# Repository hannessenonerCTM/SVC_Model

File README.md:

# SVC_Model
A SVC (Static Var Compensation) model for a Educational usecase
To be used with a 110kV overhead line model operated at 1/1000 of the voltage.
Includes 3 TCC (Thyristor Controlled Capacitance) controlled via a 5V SELV control network, optionally a ATMega32U4 can be used for grid voltage regulation. A 5V PSU is included on board. There are no input filters to show the effect of a bad THDi.

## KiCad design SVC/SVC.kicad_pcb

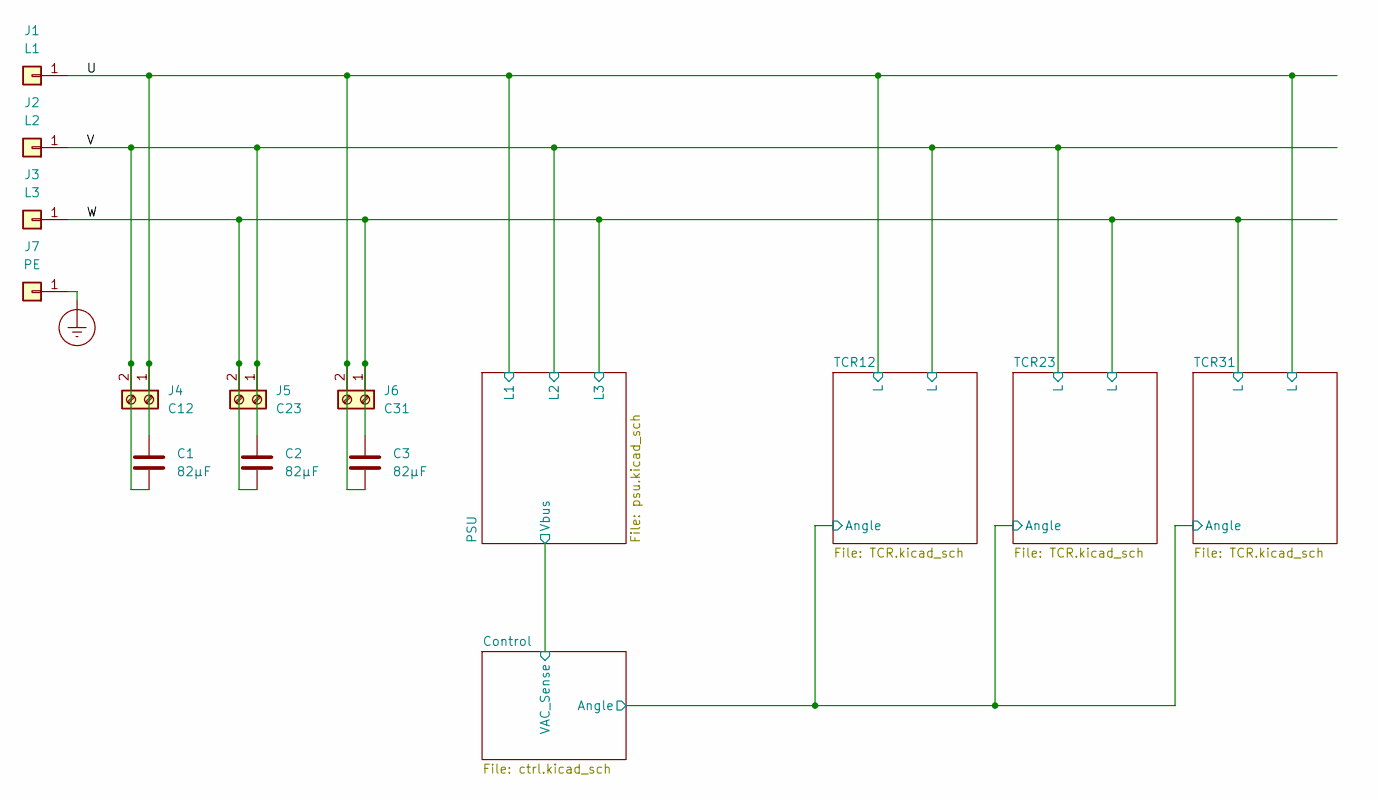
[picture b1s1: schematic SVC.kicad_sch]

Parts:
C1, C2, C3: 82µF
J1: L1; Banana_Jack_1Pin
J2: L2; Banana_Jack_1Pin
J3: L3; Banana_Jack_1Pin
J4: C12; TerminalBlock_bornier-2_P5.08mm
J5: C23; TerminalBlock_bornier-2_P5.08mm
J6: C31; TerminalBlock_bornier-2_P5.08mm
J7: PE; Banana_Jack_1Pin

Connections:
/U: C1.1, C3.2, J1.1, J4.1, J6.2; also elsewhere on the board
/V: C1.2, C2.1, J2.1, J4.2, J5.1; also elsewhere on the board
/W: C2.2, C3.1, J3.1, J5.2, J6.1; also elsewhere on the board
Earth_Protective: J7.1; also elsewhere on the board

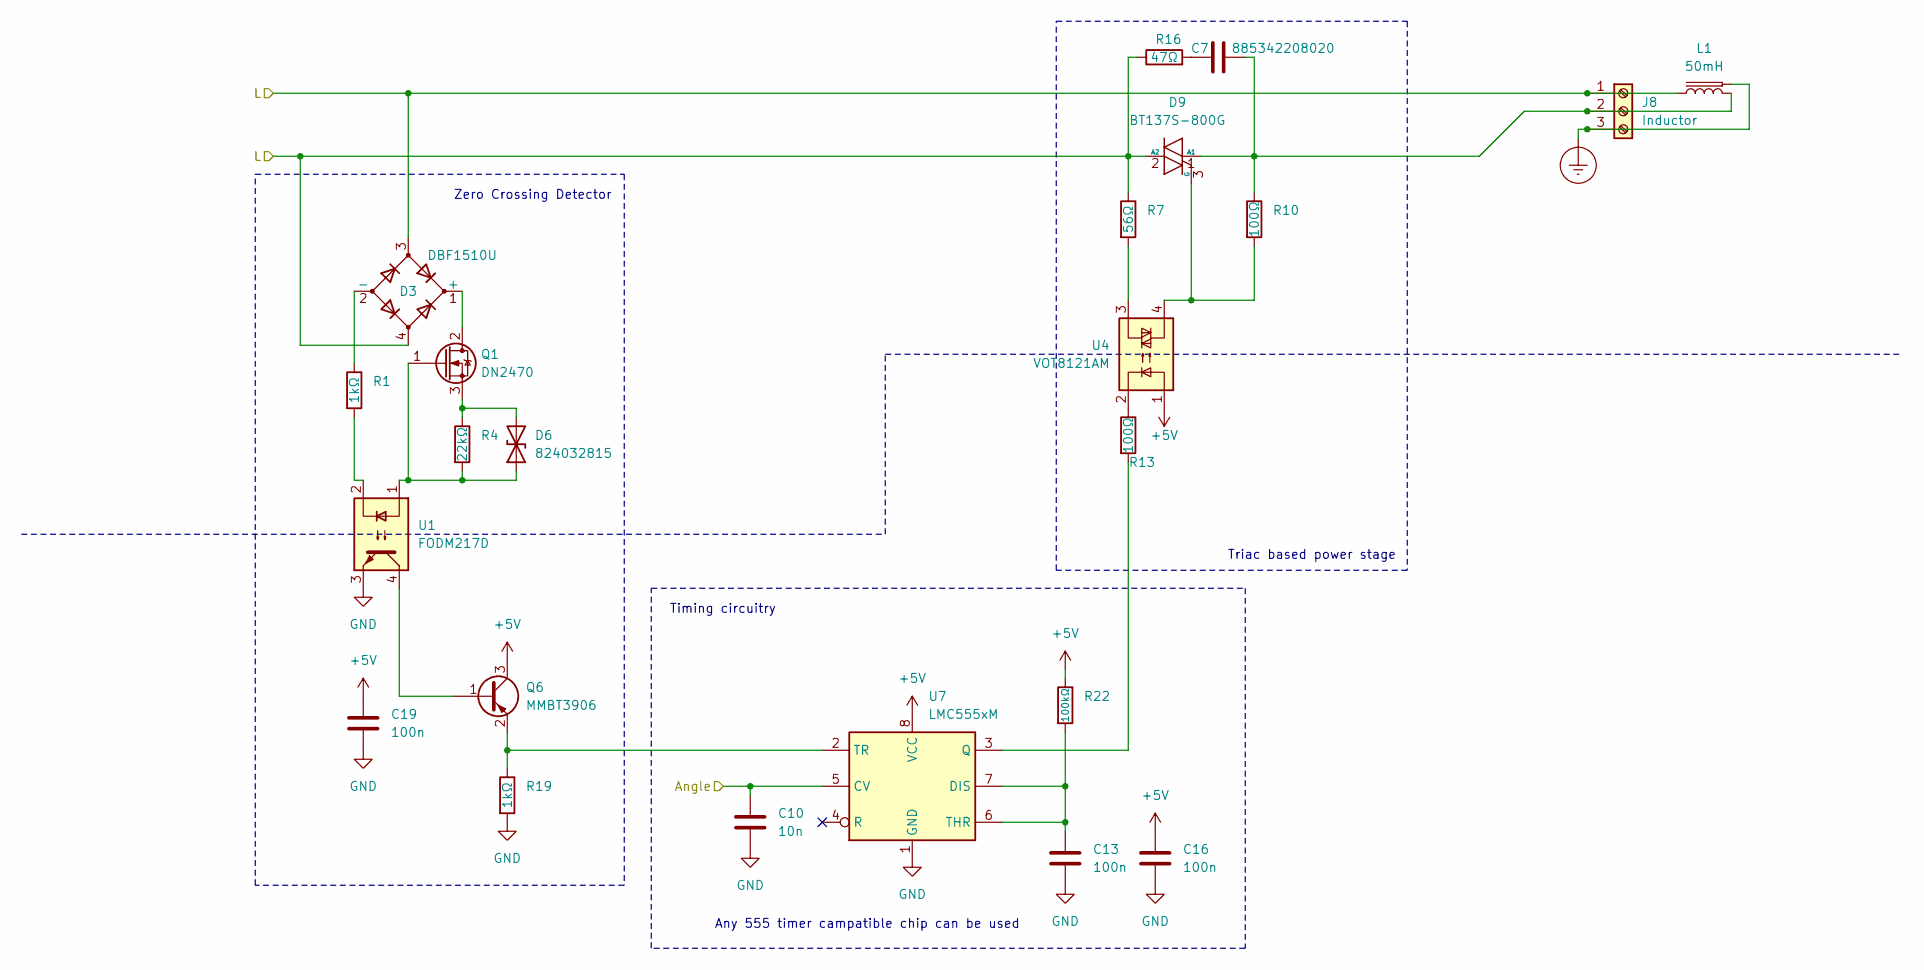
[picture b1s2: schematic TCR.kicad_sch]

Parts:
C7: 885342208020; C_1206_3216Metric
C10: 10n; C_0805_2012Metric
C13, C16, C19: 100n; C_0805_2012Metric
D3: DBF1510U; Diode_Bridge_Diotec_SO-DIL-Slim
D6: 824032815; TVS
D9: BT137S-800G; TO-252-2
J8: Inductor; TerminalBlock_bornier-3_P5.08mm
L1: 50mH
Q1: DN2470; TO-252-2
Q6: MMBT3906; SOT-23
R1, R19: 1kΩ; R_0805_2012Metric
R4: 22kΩ; R_0805_2012Metric
R7: 56Ω; R_1206_3216Metric
R10, R13: 100Ω; R_1206_3216Metric
R16: 47Ω; R_1210_3225Metric
R22: 100kΩ; R_0805_2012Metric
U1: FODM217D; SOP-4_4.4x2.6mm_P1.27mm
U4: VOT8121AM; SOP-4_3.8x4.1mm_P2.54mm
U7: LMC555xM; SOIC-8_3.9x4.9mm_P1.27mm

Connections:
+5V: C16.1, C19.1, Q6.3 (C), R22.1, U4.1, U7.8 (VCC); also elsewhere on the board
/Control/Angle: C10.1, U7.5 (CV); also elsewhere on the board
/U: D3.3, J8.1; also elsewhere on the board
/V: D3.4, D9.2 (A2), R7.1, R16.1; also elsewhere on the board
Earth_Protective: J8.3, L1.2; also elsewhere on the board
GND: C10.2, C13.2, C16.2, C19.2, R19.2, U1.3, U7.1 (GND); also elsewhere on the board
unnamed: C7.1, R16.2
unnamed: D3.1 (+), Q1.2 (D)
unnamed: D3.2 (-), R1.1
unnamed: D6.1 (A1), Q1.1 (G), R4.2, U1.1
unnamed: D6.2 (A2), Q1.3 (S), R4.1
unnamed: C7.2, D9.1 (A1), J8.2, R10.1
unnamed: D9.3 (G), R10.2, U4.4
unnamed: R1.2, U1.2
unnamed: R7.2, U4.3
unnamed: R13.1, U4.2
unnamed: C13.1, R22.2, U7.6 (THR), U7.7 (DIS)
unnamed: R13.2, U7.3 (Q)

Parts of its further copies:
C8, C9: 885342208020; C_1206_3216Metric
C11, C12: 10n; C_0805_2012Metric
C14, C15, C17, C18, C20, C21: 100n; C_0805_2012Metric
D4, D5: DBF1510U; Diode_Bridge_Diotec_SO-DIL-Slim
D7, D8: 824032815; TVS
D10, D11: BT137S-800G; TO-252-2
J9, J10: Inductor; TerminalBlock_bornier-3_P5.08mm
Q2, Q3: DN2470; TO-252-2
Q4, Q5: MMBT3906; SOT-23
R2, R3, R20, R21: 1kΩ; R_0805_2012Metric
R5, R6: 22kΩ; R_0805_2012Metric
R8, R9: 56Ω; R_1206_3216Metric
R11, R12, R14, R15: 100Ω; R_1206_3216Metric
R17, R18: 47Ω; R_1210_3225Metric
R23, R24: 100kΩ; R_0805_2012Metric
U2, U3: FODM217D; SOP-4_4.4x2.6mm_P1.27mm
U5, U6: VOT8121AM; SOP-4_3.8x4.1mm_P2.54mm
U8, U9: LMC555xM; SOIC-8_3.9x4.9mm_P1.27mm

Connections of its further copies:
+5V: C17.1, C18.1, C20.1, C21.1, Q4.3 (C), Q5.3 (C), R23.1, R24.1, U5.1, U6.1, U8.8 (VCC), U9.8 (VCC); also elsewhere on the board
/Control/Angle: C11.1, C12.1, U8.5 (CV), U9.5 (CV); also elsewhere on the board
/U: D5.4, D11.2 (A2), R9.1, R18.1; also elsewhere on the board
/V: D4.3, J9.1; also elsewhere on the board
/W: D4.4, D5.3, D10.2 (A2), J10.1, R8.1, R17.1; also elsewhere on the board
Earth_Protective: J9.3, J10.3; also elsewhere on the board
GND: C11.2, C12.2, C14.2, C15.2, C17.2, C18.2, C20.2, C21.2, R20.2, R21.2, U2.3, U3.3, U8.1 (GND), U9.1 (GND); also elsewhere on the board
unnamed: C8.1, R17.2
unnamed: C9.1, R18.2
unnamed: D4.1 (+), Q2.2 (D)
unnamed: D4.2 (-), R2.1
unnamed: D5.1 (+), Q3.2 (D)
unnamed: D5.2 (-), R3.1
unnamed: D7.1 (A1), Q2.1 (G), R5.2, U2.1
unnamed: D7.2 (A2), Q2.3 (S), R5.1
unnamed: D8.1 (A1), Q3.1 (G), R6.2, U3.1
unnamed: D8.2 (A2), Q3.3 (S), R6.1
unnamed: C8.2, D10.1 (A1), J9.2, R11.1
unnamed: D10.3 (G), R11.2, U5.4
unnamed: C9.2, D11.1 (A1), J10.2, R12.1
unnamed: D11.3 (G), R12.2, U6.4
unnamed: Q5.1 (B), U2.4
unnamed: Q5.2 (E), R20.1, U8.2 (TR)
unnamed: R2.2, U2.2
unnamed: R3.2, U3.2
unnamed: R8.2, U5.3
unnamed: R9.2, U6.3
unnamed: R14.1, U5.2
unnamed: R15.1, U6.2
unnamed: C14.1, R23.2, U8.6 (THR), U8.7 (DIS)
unnamed: R14.2, U8.3 (Q)
unnamed: C15.1, R24.2, U9.6 (THR), U9.7 (DIS)
unnamed: R15.2, U9.3 (Q)

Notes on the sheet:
Timing circuitry
Any 555 timer campatible chip can be used
Zero Crossing Detector
Triac based power stage

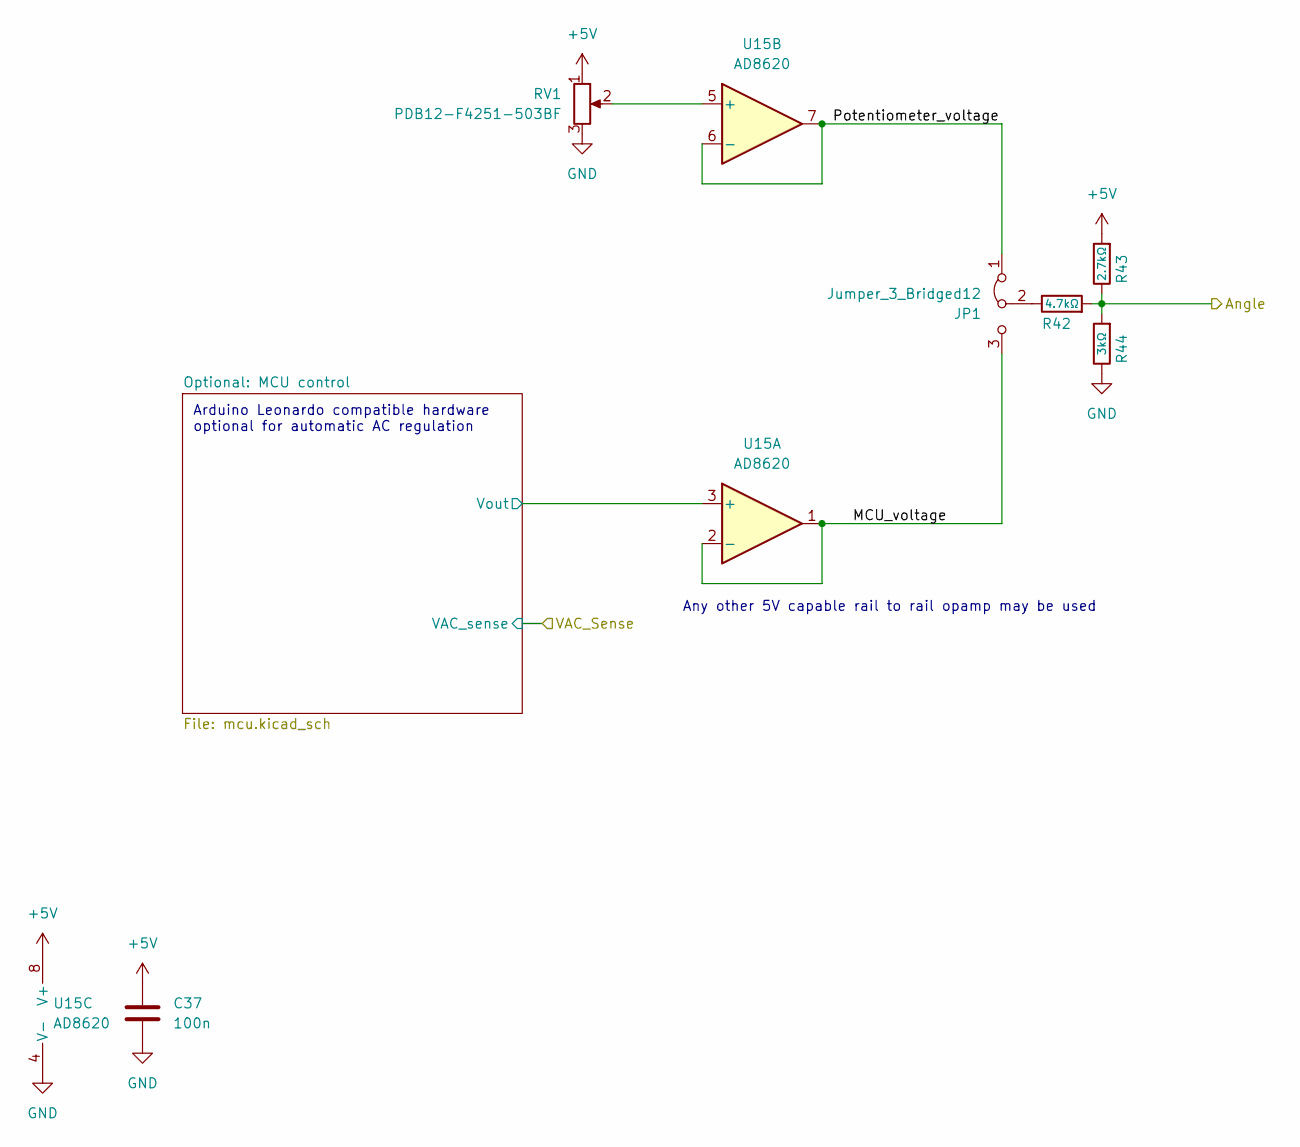
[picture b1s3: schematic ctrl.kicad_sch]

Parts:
C37: 100n; C_0805_2012Metric
JP1: Jumper_3_Bridged12; PinHeader_1x03_P2.54mm_Vertical
R42: 4.7kΩ; R_0805_2012Metric
R43: 2.7kΩ; R_0805_2012Metric
R44: 3kΩ; R_0805_2012Metric
RV1: PDB12-F4251-503BF; Bourns PDB12
U15: AD8620; SOIC-8_3.9x4.9mm_P1.27mm

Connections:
+5V: C37.1, R43.2, RV1.1, U15.8 (V+); also elsewhere on the board
/Control/Angle: R42.2, R43.1, R44.2; also elsewhere on the board
/Control/MCU_voltage: JP1.3 (B), U15.1, U15.2 (-)
/Control/Optional: MCU control/Vout: U15.3 (+); also elsewhere on the board
/Control/Potentiometer_voltage: JP1.1 (A), U15.6 (-), U15.7
GND: C37.2, R44.1, RV1.3, U15.4 (V-); also elsewhere on the board
unnamed: JP1.2 (C), R42.1
unnamed: RV1.2, U15.5 (+)

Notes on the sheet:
Arduino Leonardo compatible hardware optional for automatic AC regulation
Any other 5V capable rail to rail opamp may be used

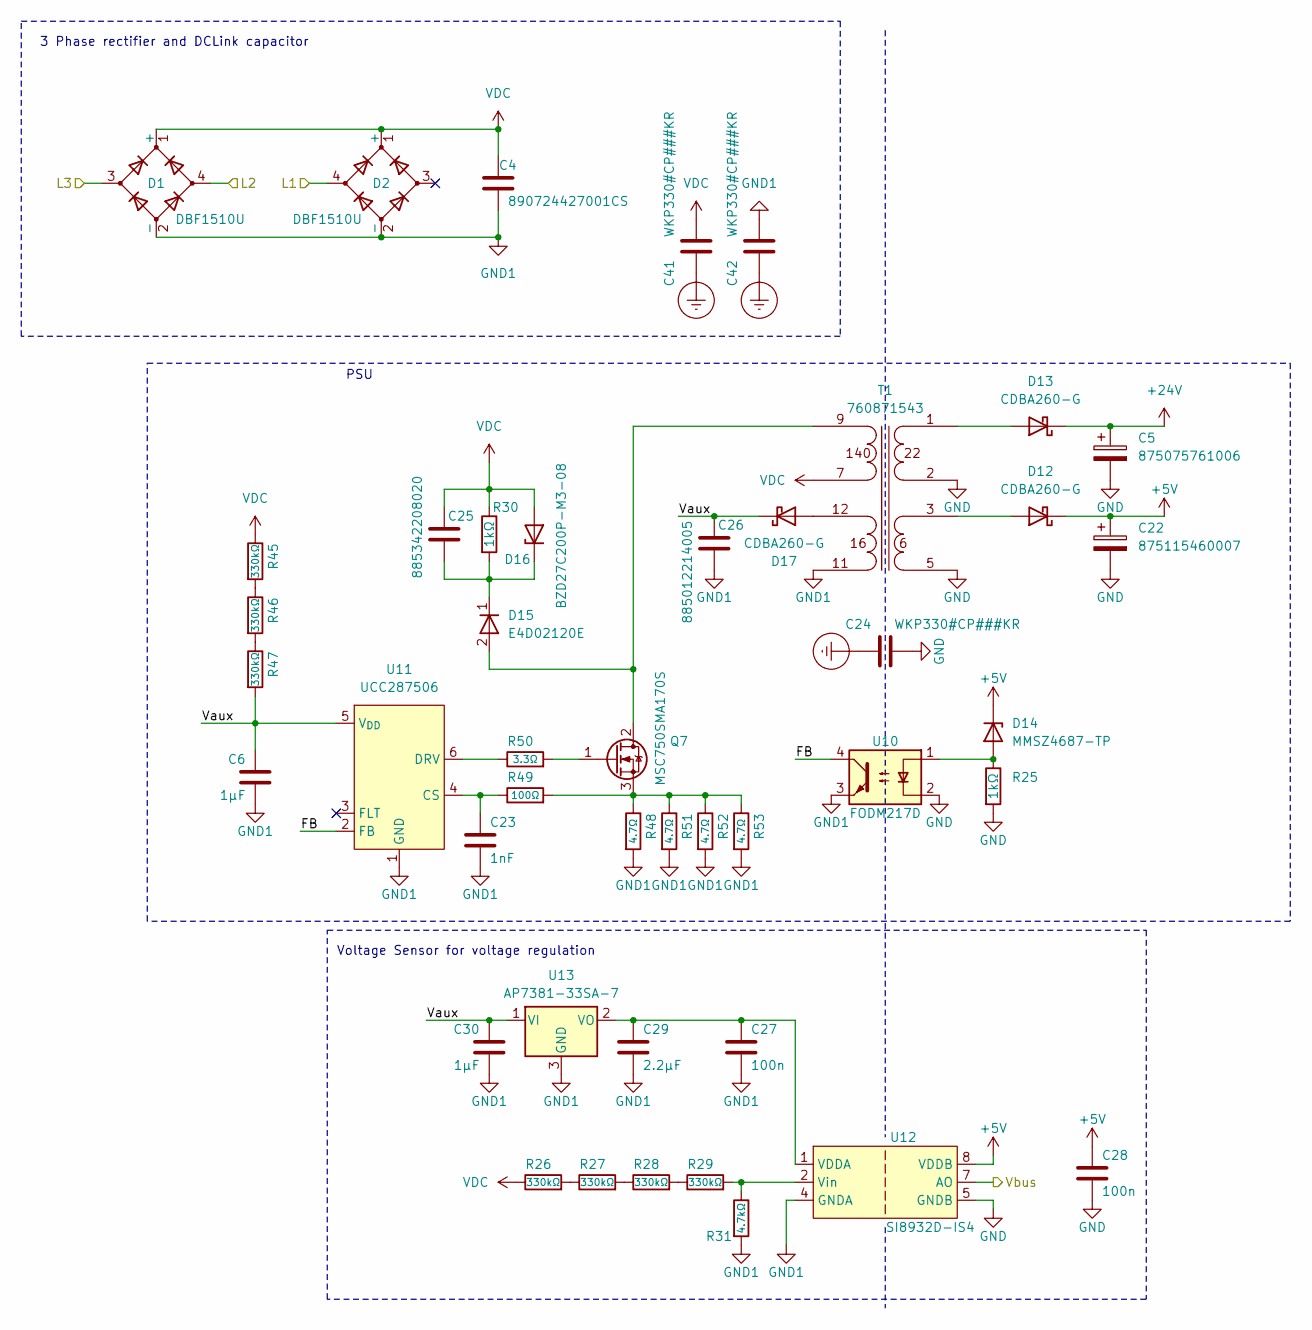
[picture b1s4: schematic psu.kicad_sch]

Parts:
C4: 890724427001CS; C_Rect_L31.5mm_W9.0mm_P27.50mm_MKS4
C5: 875075761006; CP_Elec_10x12.5
C6, C30: 1µF; C_0805_2012Metric
C22: 875115460007; CP_Elec_10x7.9
C23: 1nF; C_0805_2012Metric
C24, C41, C42: WKP330#CP###KR
C25: 885342208020; C_1206_3216Metric
C26: 885012214005; C_1206_3216Metric
C27, C28: 100n; C_0805_2012Metric
C29: 2.2µF; C_0805_2012Metric
D1, D2: DBF1510U; Diode_Bridge_Diotec_SO-DIL-Slim
D12, D13, D17: CDBA260-G; D_SMA
D14: MMSZ4687-TP; D_SOD-123
D15: E4D02120E; TO-252-2_TabPin1
D16: BZD27C200P-M3-08; D_SMF
Q7: MSC750SMA170S; TO-252-2
R25: 1kΩ; R_0805_2012Metric
R26, R27, R28, R29, R45, R46, R47: 330kΩ; R_0805_2012Metric
R30: 1kΩ; R_1206_3216Metric
R31: 4.7kΩ; R_0805_2012Metric
R48, R51, R52, R53: 4.7Ω; R_0805_2012Metric
R49: 100Ω; R_0805_2012Metric
R50: 3.3Ω; R_0805_2012Metric
T1: 760871543
U10: FODM217D; SOP-4_4.4x2.6mm_P1.27mm
U11: UCC287506; SOT-23-6
U12: SI8932D-IS4; SOIC-8_7.5x5.85mm_P1.27mm
U13: AP7381-33SA-7; SOT-23

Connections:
+5V: C22.1, C28.1, D12.1 (K), D14.1 (K), U12.8 (VDDB); also elsewhere on the board
+24V: C5.1, D13.1 (K); also elsewhere on the board
/Control/Optional: MCU control/Arduino Pin A0 ADC: U12.7 (AO); also elsewhere on the board
/PSU/FB: U10.4, U11.2 (FB)
/PSU/Vaux: C6.1, C26.1, C30.1, D17.1 (K), R47.2, U11.5 (V_{DD}), U13.1 (VI)
/U: D2.4; also elsewhere on the board
/V: D1.4; also elsewhere on the board
/W: D1.3; also elsewhere on the board
Earth_Protective: C24.1, C41.1, C42.1; also elsewhere on the board
GND: C5.2, C22.2, C24.2, C28.2, R25.2, T1.2 (OUT1B), T1.5 (OUT2B), T1.6 (OUT2B), U10.2, U12.5 (GNDB), U12.6 (GNDB); also elsewhere on the board
GND1: C4.2, C6.2, C23.2, C26.2, C27.2, C29.2, C30.2, C42.2, D1.2 (-), D2.2 (-), R31.2, R48.2, R51.2, R52.2, R53.2, T1.11 (IN-), U10.3, U11.1 (GND), U12.4 (GNDA), U13.3 (GND)
unnamed: D12.2 (A), T1.3 (OUT2A), T1.4 (OUT2A)
unnamed: D13.2 (A), T1.1 (OUT1A)
unnamed: D14.2 (A), R25.1, U10.1
unnamed: D15.2 (A), Q7.2 (D), T1.9 (IN+)
unnamed: C25.2, D15.1 (K), D16.1 (K), R30.2
unnamed: D17.2 (A), T1.12 (IN+)
unnamed: Q7.1 (G), R50.2
unnamed: Q7.3 (S), R48.1, R49.2, R51.1, R52.1, R53.1
unnamed: R26.2, R27.1
unnamed: R27.2, R28.1
unnamed: R28.2, R29.1
unnamed: R45.2, R46.1
unnamed: R46.2, R47.1
unnamed: C23.1, R49.1, U11.4 (CS)
unnamed: R50.1, U11.6 (DRV)
unnamed: C27.1, C29.1, U12.1 (VDDA), U13.2 (VO)
unnamed: R29.2, R31.1, U12.2 (Vin)
VDC: C4.1, C25.1, C41.2, D1.1 (+), D2.1 (+), D16.2 (A), R26.1, R30.1, R45.1, T1.7 (IN-)

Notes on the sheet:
Voltage Sensor for voltage regulation
PSU
3 Phase rectifier and DCLink capacitor

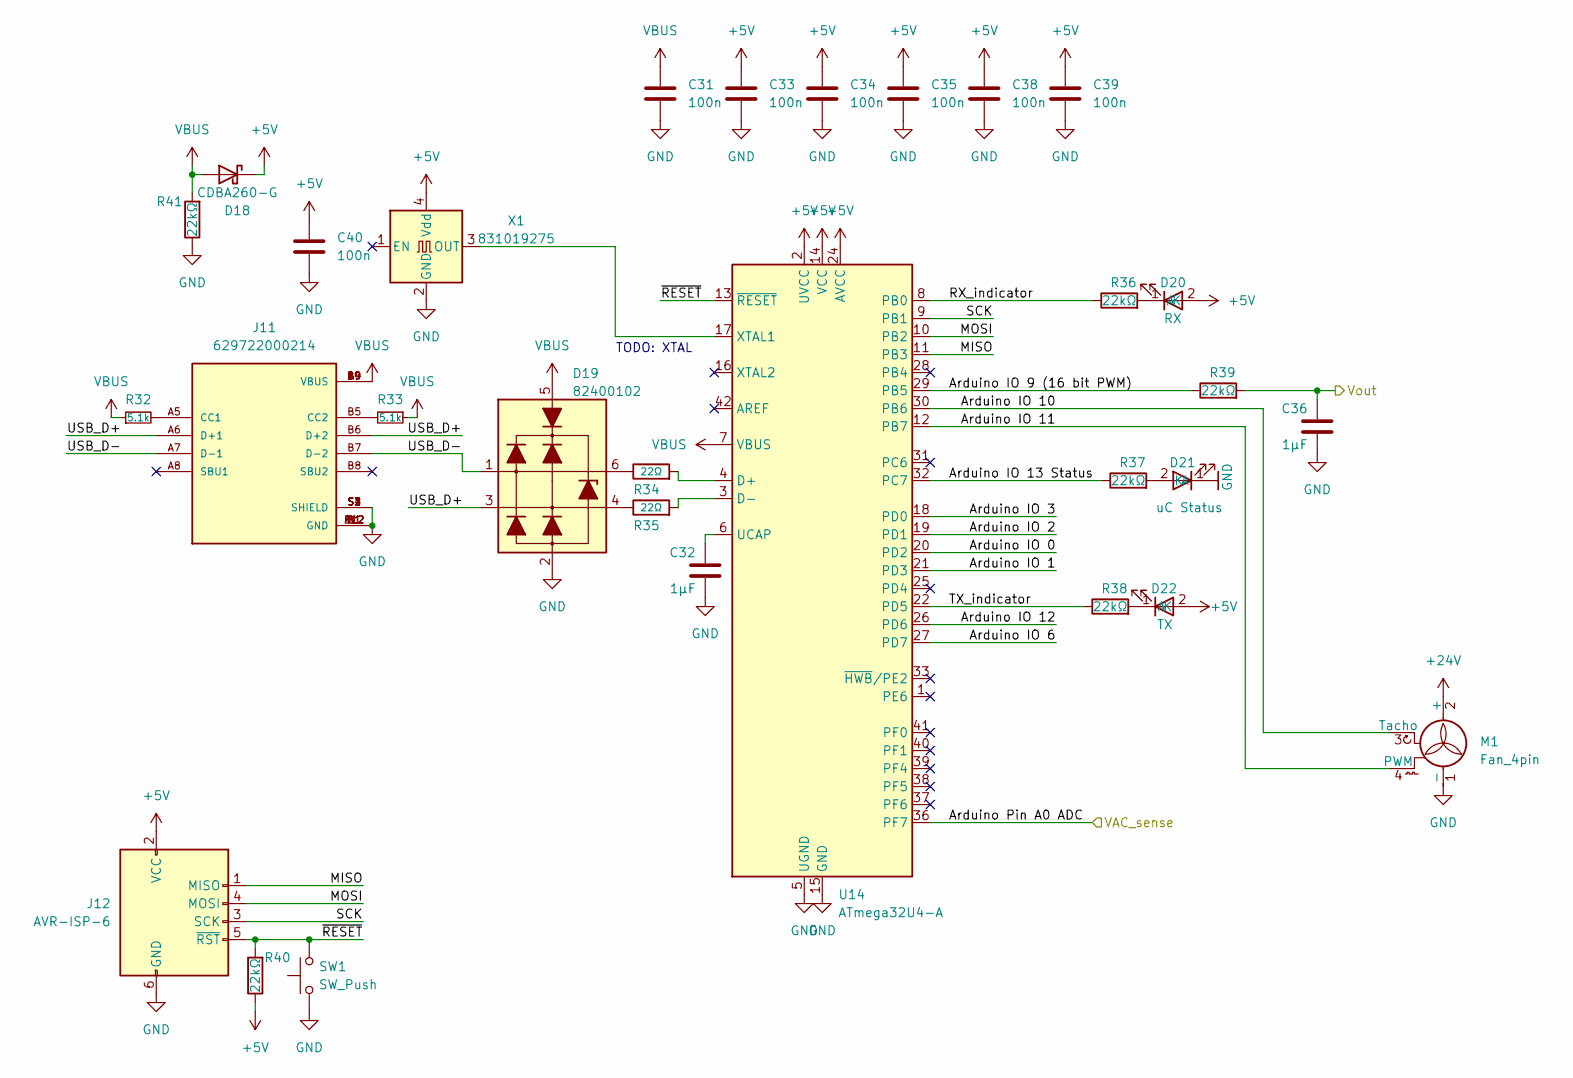
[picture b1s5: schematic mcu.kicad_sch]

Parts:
C31, C33, C34, C35, C38, C39, C40: 100n; C_0805_2012Metric
C32, C36: 1µF; C_0805_2012Metric
D18: CDBA260-G; D_SMA
D19: 82400102; SOT-23-6_Handsoldering
D20: RX; LED_0805_2012Metric_Pad1.15x1.40mm_HandSolder
D21: uC Status; LED_0805_2012Metric_Pad1.15x1.40mm_HandSolder
D22: TX; LED_0805_2012Metric_Pad1.15x1.40mm_HandSolder
J11: 629722000214; PARTREV 001.001
J12: AVR-ISP-6; PinHeader_2x03_P2.54mm_Vertical
M1: Fan_4pin; FanPinHeader_1x04_P2.54mm_Vertical
R32, R33: 5.1k; R_0805_2012Metric_Pad1.20x1.40mm_HandSolder
R34, R35: 22Ω; R_0805_2012Metric
R36, R37, R38, R39, R40, R41: 22kΩ; R_0805_2012Metric
SW1: SW_Push; SW_Push_1P1T_NO_6x6mm_H9.5mm
U14: ATmega32U4-A; TQFP-44_10x10mm_P0.8mm
X1: 831019275; Oscillator_SMD_Abracon_ASV-4Pin_7.0x5.1mm

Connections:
+5V: C33.1, C34.1, C35.1, C38.1, C39.1, C40.1, D18.1 (K), D20.2 (A), D22.2 (A), J12.2 (VCC), R40.1, U14.2 (UVCC), U14.14 (VCC), U14.24 (AVCC), U14.34 (VCC), U14.44 (AVCC), X1.4 (Vdd); also elsewhere on the board
+24V: M1.2 (+); also elsewhere on the board
/Control/Optional: MCU control/Arduino IO 0: U14.20 (PD2)
/Control/Optional: MCU control/Arduino IO 1: U14.21 (PD3)
/Control/Optional: MCU control/Arduino IO 2: U14.19 (PD1)
/Control/Optional: MCU control/Arduino IO 3: U14.18 (PD0)
/Control/Optional: MCU control/Arduino IO 6: U14.27 (PD7)
/Control/Optional: MCU control/Arduino IO 9 (16 bit PWM): R39.1, U14.29 (PB5)
/Control/Optional: MCU control/Arduino IO 10: M1.3 (Tacho), U14.30 (PB6)
/Control/Optional: MCU control/Arduino IO 11: M1.4 (PWM), U14.12 (PB7)
/Control/Optional: MCU control/Arduino IO 12: U14.26 (PD6)
/Control/Optional: MCU control/Arduino IO 13 Status: R37.1, U14.32 (PC7)
/Control/Optional: MCU control/Arduino Pin A0 ADC: U14.36 (PF7); also elsewhere on the board
/Control/Optional: MCU control/MISO: J12.1 (MISO), U14.11 (PB3)
/Control/Optional: MCU control/MOSI: J12.4 (MOSI), U14.10 (PB2)
/Control/Optional: MCU control/RX_indicator: R36.1, U14.8 (PB0)
/Control/Optional: MCU control/SCK: J12.3 (SCK), U14.9 (PB1)
/Control/Optional: MCU control/TX_indicator: R38.1, U14.22 (PD5)
/Control/Optional: MCU control/USB_D+: D19.3 (L2), J11.A6 (D+1), J11.B6 (D+2)
/Control/Optional: MCU control/USB_D-: D19.1 (L1), J11.A7 (D-1), J11.B7 (D-2)
/Control/Optional: MCU control/Vout: C36.1, R39.2; also elsewhere on the board
/Control/Optional: MCU control/~RESET: J12.5 (~RST), R40.2, SW1.2, U14.13 (~RESET)
GND: C31.2, C32.2, C33.2, C34.2, C35.2, C36.2, C38.2, C39.2, C40.2, D19.2 (VN), D21.1 (K), J11.A1 (GND), J11.A12 (GND), J11.B1 (GND), J11.B12 (GND), J11.S1 (SHIELD), J11.S2 (SHIELD), J11.S3 (SHIELD), J11.S4 (SHIELD), J12.6 (GND), M1.1 (-), R41.1, SW1.1, U14.5 (UGND), U14.15 (GND), U14.23 (GND), U14.35 (GND), U14.43 (GND), X1.2 (GND); also elsewhere on the board
unnamed: D19.6 (L1), R34.1
unnamed: D19.4 (L2), R35.1
unnamed: D20.1 (K), R36.2
unnamed: D21.2 (A), R37.2
unnamed: D22.1 (K), R38.2
unnamed: J11.A5 (CC1), R32.2
unnamed: J11.B5 (CC2), R33.2
unnamed: R34.2, U14.4 (D+)
unnamed: R35.2, U14.3 (D-)
unnamed: C32.1, U14.6 (UCAP)
unnamed: U14.17 (XTAL1), X1.3 (OUT)
VBUS: C31.1, D18.2 (A), D19.5 (VP), J11.A4 (VBUS), J11.A9 (VBUS), J11.B4 (VBUS), J11.B9 (VBUS), R32.1, R33.1, R41.2, U14.7 (VBUS)

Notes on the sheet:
TODO: XTAL

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
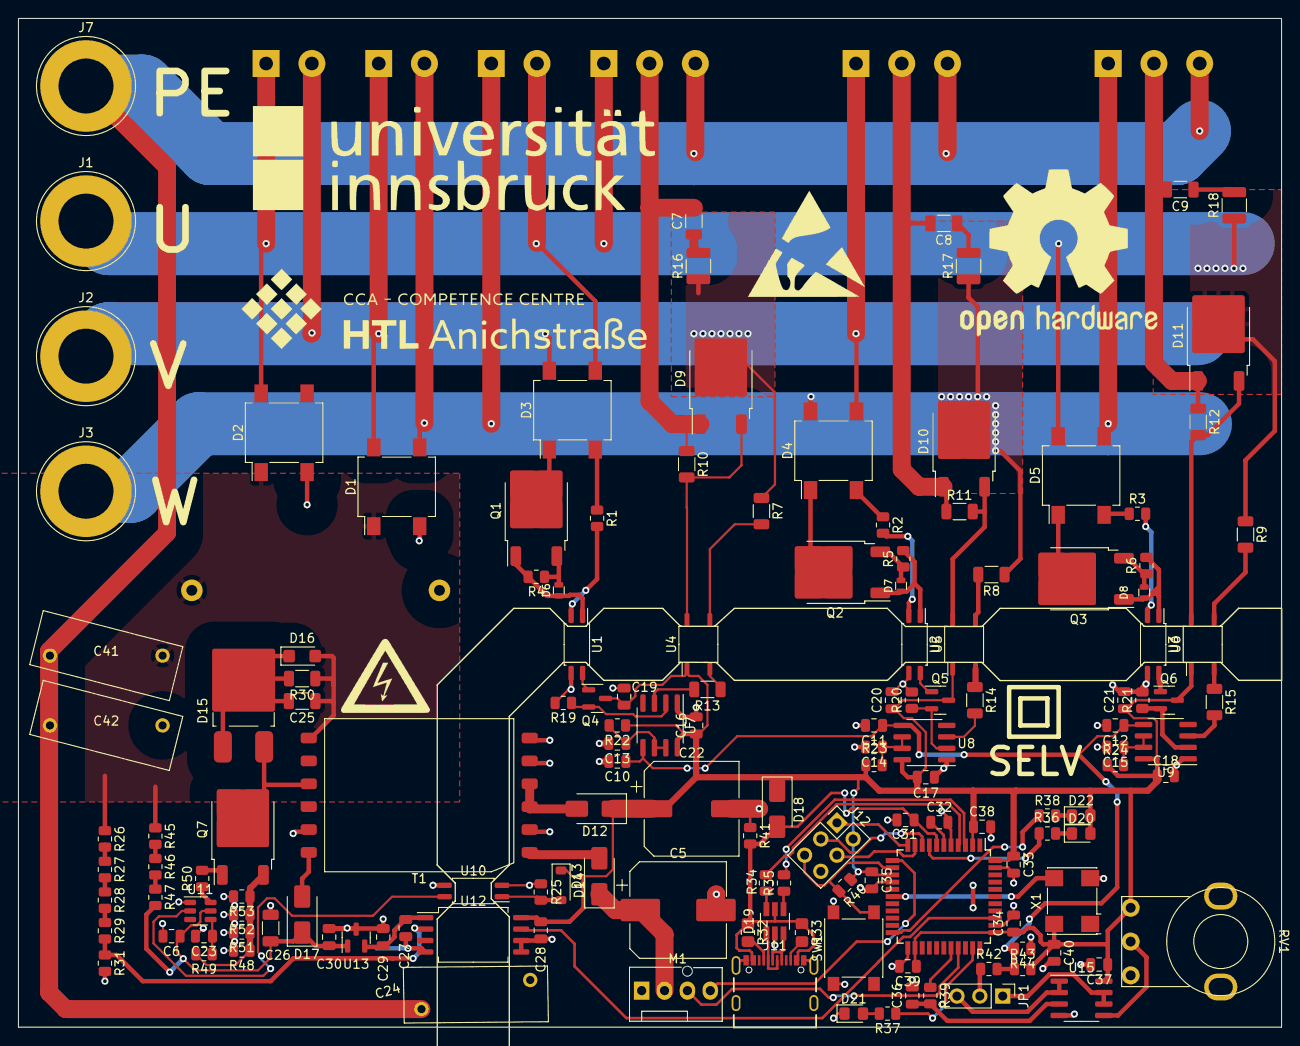
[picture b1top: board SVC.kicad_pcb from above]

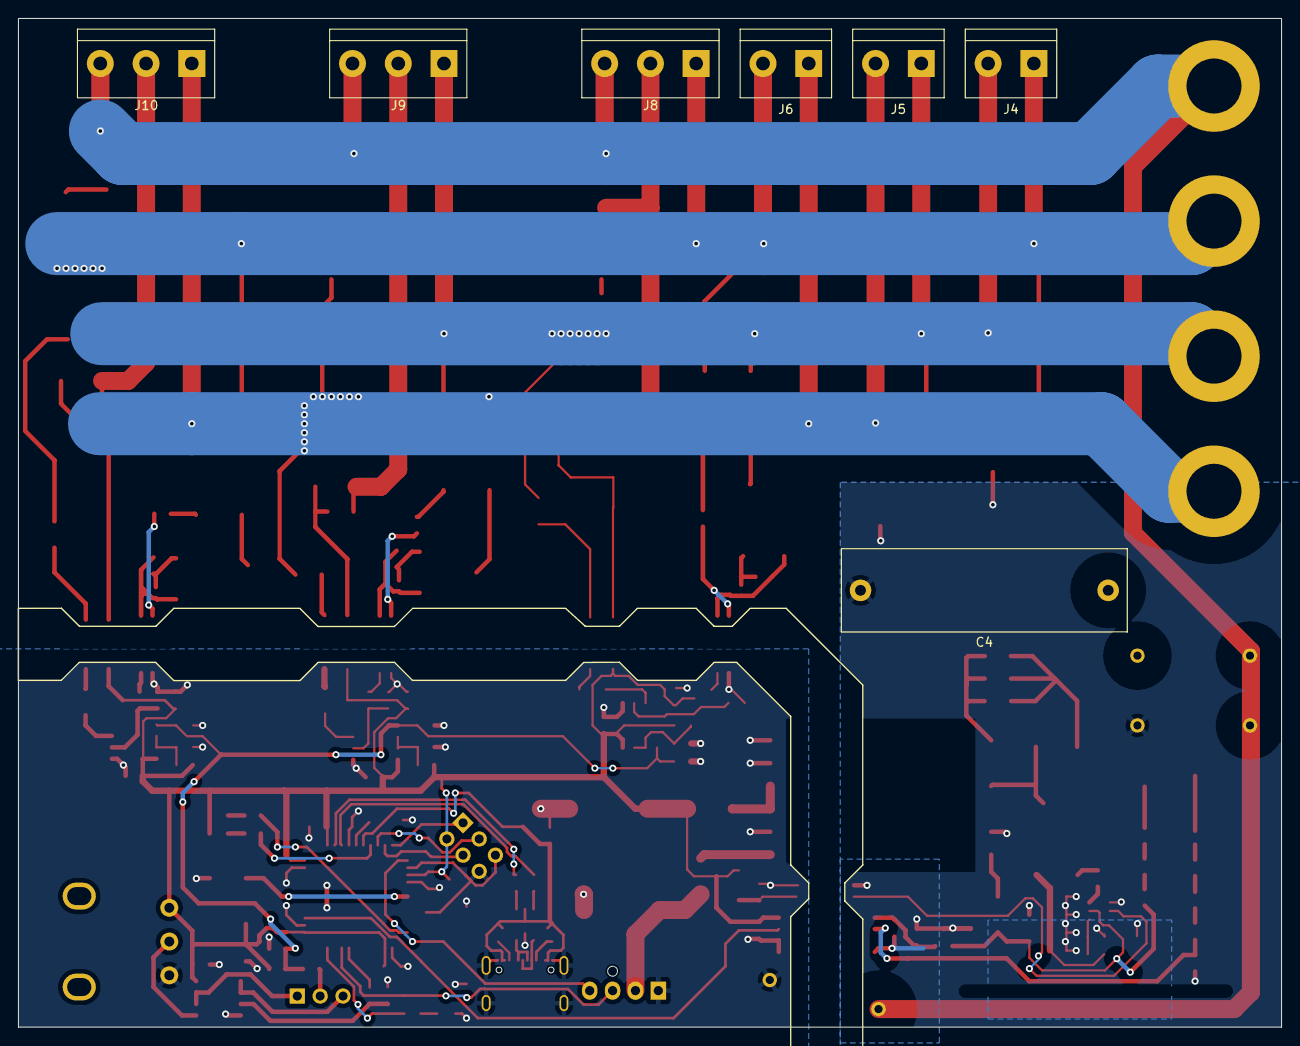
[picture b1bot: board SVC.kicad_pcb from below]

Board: 2 copper layers, 140.2 x 112.0 mm, 154 parts (7 on the bottom side), 101 nets.

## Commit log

2024-02-13 Update README.md
    Added extra details about the project
2024-02-14 Added simulation model, drawn schematic
2024-02-21 did some layout work, minor schematic changes to help with layout
2024-02-22 added some symbols, marked LV area as SELV
